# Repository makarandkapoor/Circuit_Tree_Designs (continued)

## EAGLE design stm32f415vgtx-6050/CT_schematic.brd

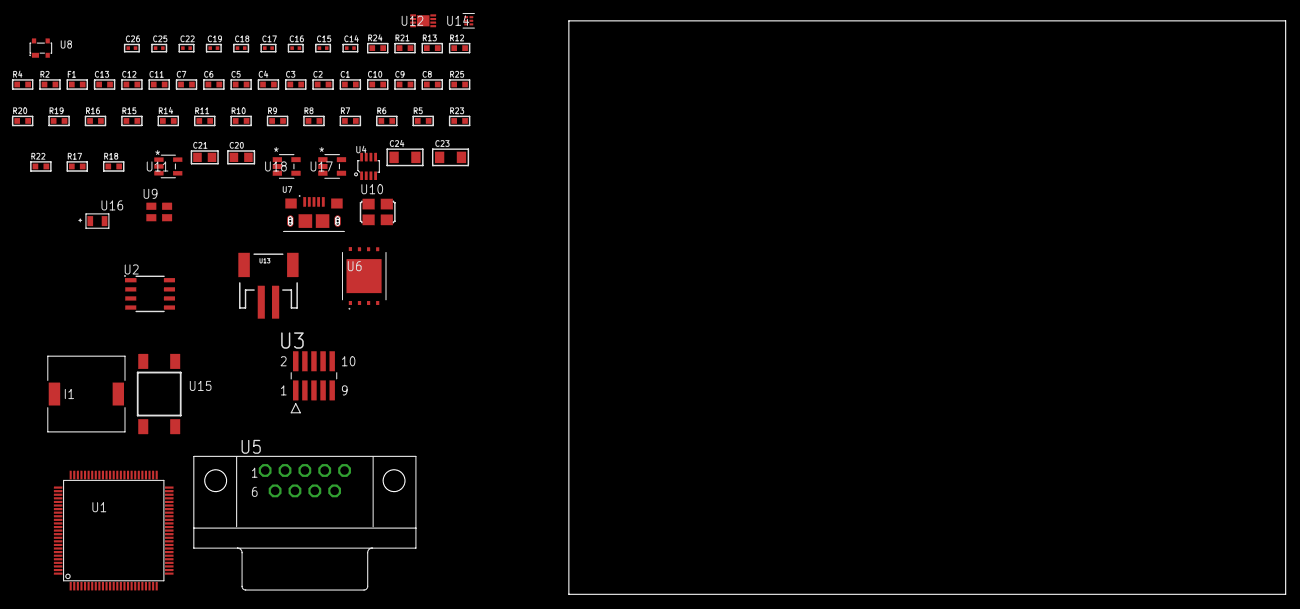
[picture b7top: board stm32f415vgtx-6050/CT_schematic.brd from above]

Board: 2 copper layers, 69 parts (0 on the bottom side), 45 nets, no tracks yet.

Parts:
C1, C12, C13: 1e-06; C0603
C2, C3, C4, C5, C6, C7: 1e-07; C0603
C8: 4.7e-06; C0603
C9, C10: 2.2e-06; C0603
C11: 1e-08; C0603
C14, C17, C18, C19, C25, C26: 1e-08; C0402
C15, C16, C22: 1e-07; C0402
C20, C21: 1e-05; C0805
C23, C24: 1e-05; C1206
F1: 240.0; L0603
I1: 2.5e-06; DR1040
R2: 1000.0; R0603
R4: 4700.0; R0603
R5, R6, R7, R8, R9, R10, R11, R14, R15, R16, R19, R20, R25: 10000.0; R0603
R12: 5.0; R0603
R13: 120.0; R0603
R17: 220000.0; R0603
R18: 1000000.0; R0603
R21: 9100.0; R0603
R22: 680000.0; R0603
R23: 120000.0; R0603
R24: 2000.0; R0603
U1: STM32F415VGT6; LQFP100
U2: AT25320B-SSHL-T; SOIC-8
U3: FTSH-105-01-L-DV-K; SAMTEC_FTSH-105-01-L-DV-K
U4: MAX3051EKA+T; SOT-23-8
U5: 182-009-113R531; 182-009-MALE
U6: S25FL128SDPNFI001; WNG008
U7: 10118193-0001LF; FCI_10118193-0001LF
U8: prtr5v0u2ax; SOT143B
U9: ASEK-32.768KHz-ECST; ASEK
U10: ASFL1-25MHZ-NCS; ASFL1
U11: ltc3406es5; TSOT-23-5
U12: MCP73831T-2ACI/MC; DFN8_2X3MC
U13: S2B-PH-SM4-TB(LF)(SN); JST-2-SMD
U14: TPS3895ADRYR; SON-6
U15: 4-1437565-2; SW_4-1437565-2
U16: Q65110A2395; LGM67K-G1J2-24-Z
U17, U18: nc7sz125m5x; NC7SZ125M5X

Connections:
CLK_U1_8: U1.8, U9.3
CLK_U1_12: U1.12, U10.3
GND: C1.2, C2.2, C3.2, C4.2, C5.2, C6.2, C7.2, C8.2, C9.2, C10.2, C11.2, C12.2, C13.2, C14.2, C15.2, C16.2, C17.2, C18.2, C19.2, C20.2, C21.1, C21.2, C22.2, C23.2, C24.2, C25.2, C26.2, R2.2, R5.2, R12.2, R17.2, R21.2, R23.2, R24.2, U1.10, U1.20, U1.27, U1.70, U1.74, U1.99, U2.4, U3.3, U3.5, U4.2, U4.8, U5.5, U6.4, U6.PAD, U7.5, U7.6, U7.7, U7.8, U7.9, U8.1, U9.2, U10.2, U11.2, U12.6, U12.9, U13.2, U14.2, U16.C, U17.2, U17.3, U18.1, U18.3
INPUT_USBPOWER_5V: C13.1, C23.1, R25.2, U1.68, U7.1, U8.4, U12.1, U12.2
NET_U1_14: R4.1, U1.14, U18.4
NET_U1_22: C11.1, C12.1, F1.1, U1.21, U1.22
NET_U1_49: C9.1, U1.49
NET_U1_73: C10.1, U1.73
NET_U1_94: R5.1, U1.94
NET_U1_98: U15.3, U15.4
NET_U2_3: R6.1, U2.3
NET_U2_7: R8.1, U2.7
NET_U3_9: R12.1, U3.9
NET_U4_6: R13.2, U4.6
NET_U5_2: R13.2, U4.6, U5.2
NET_U5_3: R13.1, U4.7, U5.3
NET_U6_3: R14.1, U6.3
NET_U6_7: R16.1, U6.7
NET_U11_3: I1.1, U11.3
NET_U11_5: R17.1, R18.1, U11.5
NET_U11_ATNET_3: I1.2, R18.2
NET_U12_5: R25.1, U12.5
NET_U12_8: R24.1, U12.8
NET_U14_1: R20.1, R21.1, U14.1
NET_U14_3: R22.2, R23.1, U14.3
NET_U14_4: R19.1, U14.4, U17.4, U18.2
NET_U15_1: R2.1, U15.1, U15.2
PROC_CAN1_RX: U1.81, U4.4
PROC_CAN1_TX: U1.82, U4.1
PROC_SPI1_MISO: U1.31, U2.2
PROC_SPI1_MOSI: U1.32, U2.5
PROC_SPI1_NSS: R7.1, U1.29, U2.1
PROC_SPI1_SCK: U1.30, U2.6
PROC_SPI2_MISO: U1.17, U6.2
PROC_SPI2_MOSI: U1.18, U6.5
PROC_SPI2_NSS: R15.1, U1.51, U6.1
PROC_SPI2_SCK: U1.47, U6.6
PROC_SYS_JTCK_SWCLK: R10.1, U1.76, U3.4
PROC_SYS_JTDO_SWO: U1.89, U3.6
PROC_SYS_JTMS_SWDIO: R11.1, U1.72, U3.2
PROC_USB_OTG_FS_DM: U1.70, U7.2, U8.3
PROC_USB_OTG_FS_DP: U1.71, U7.3, U8.2
RST_OUT_U3_JTAG_RST_B: R9.1, U3.10, U17.1
VCC_S1_3V7: C20.1, C24.1, U11.4, U12.3, U12.4, U13.1
VCC_TIER1_3V3: C1.1, C2.1, C3.1, C4.1, C5.1, C6.1, C7.1, C8.1, C14.1, C15.1, C16.1, C17.1, C18.1, C19.1, C21.2, C22.1, C25.1, C26.1, F1.2, I1.2, R4.2, R6.2, R7.2, R8.2, R9.2, R10.2, R11.2, R14.2, R15.2, R16.2, R18.2, R19.2, R20.2, R22.1, U1.6, U1.11, U1.19, U1.28, U1.50, U1.75, U1.100, U2.8, U3.1, U4.3, U6.8, U9.4, U10.4, U14.6, U17.5, U18.5

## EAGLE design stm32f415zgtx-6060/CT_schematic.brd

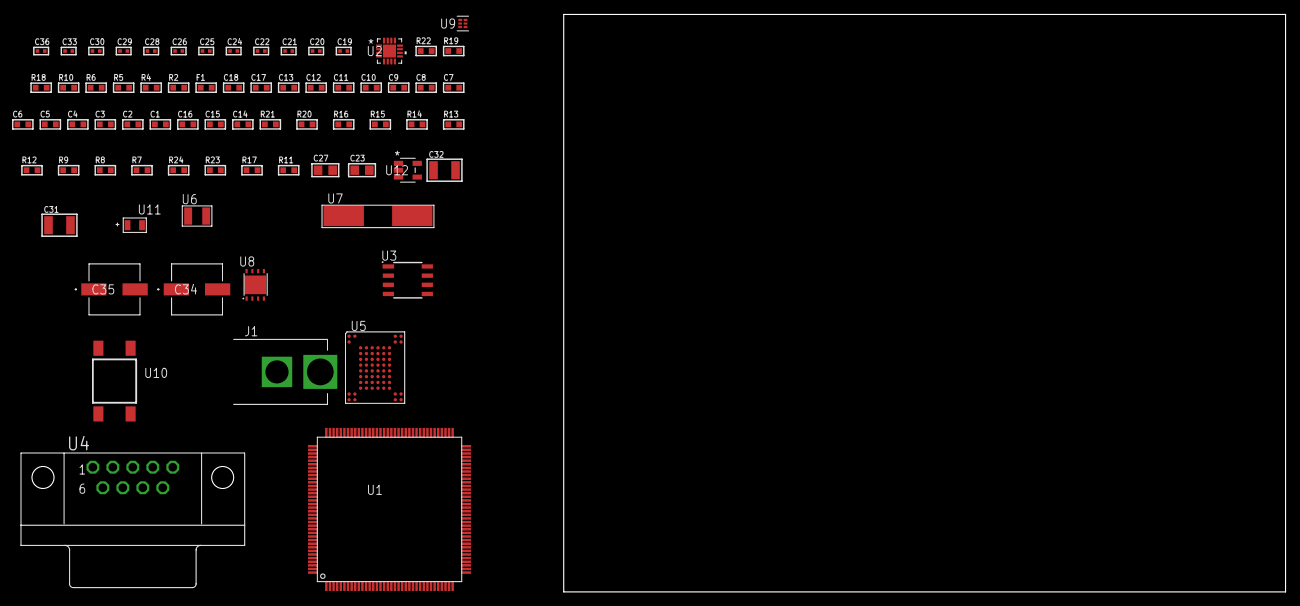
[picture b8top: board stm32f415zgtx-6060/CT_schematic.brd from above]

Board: 2 copper layers, 100.0 x 80.0 mm, 72 parts (0 on the bottom side), 46 nets, no tracks yet.

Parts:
C1, C18: 1e-06; C0603
C2, C3, C4, C5, C6, C7, C8, C9, C10, C11, C12, C13: 1e-07; C0603
C14: 4.7e-06; C0603
C15, C16: 2.2e-06; C0603
C17: 1e-08; C0603
C19, C20, C21, C22: 1e-11; C0402
C23: 4.7e-06; C0805
C24, C25, C26, C28, C29, C33: 1e-07; C0402
C27: 1e-05; C0805
C30, C36: 1e-08; C0402
C31, C32: 1e-05; C1210
C34, C35: 0.0001; EXV-9H
F1: 240.0; L0603
J1: PJ-037B; PJ-037B_PACKAGE
R2, R19: 1000.0; R0603
R4: 4700.0; R0603
R5, R6: 2200.0; R0603
R7, R8, R9, R12, R13, R14, R15, R16, R20, R21: 10000.0; R0603
R10: 120.0; R0603
R11, R17: 100000.0; R0603
R18: 2231.0; R0603
R22: 9100.0; R0603
R23: 680000.0; R0603
R24: 120000.0; R0603
U1: STM32F415ZGT6; LQFP144
U2: MMA8451QT; QFN-16
U3: SN65HVD230D; SOIC-8
U4: 182-009-113R531; 182-009-MALE
U5: TH58NVG3S0HBAI4
U6: ABS07-32.768KHZ-7-T
U7: ABLS-25.000MHZ-B2F-T
U8: LP3878SDX-ADJ/NOPB; WSON-8
U9: TPS3895ADRYR; SON-6
U10: 4-1437565-2; SW_4-1437565-2
U11: Q65110A2395; LGM67K-G1J2-24-Z
U12: nc7sz125m5x; NC7SZ125M5X

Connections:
CLK_CRYSTAL_U1_8: C19.1, U1.8, U6.1
CLK_CRYSTAL_U1_9: C20.1, U1.9, U6.2
CLK_CRYSTAL_U1_23: C21.1, U1.23, U7.1
CLK_CRYSTAL_U1_24: C22.1, U1.24, U7.2
GND: C1.2, C2.2, C3.2, C4.2, C5.2, C6.2, C7.2, C8.2, C9.2, C10.2, C11.2, C12.2, C13.2, C14.2, C15.2, C16.2, C17.2, C18.2, C19.2, C20.2, C21.2, C22.2, C23.2, C24.2, C25.2, C26.2, C27.2, C28.2, C29.2, C30.2, C31.2, C32.2, C33.2, C34.2, C35.2, C36.2, J1.2, R2.2, R8.2, R11.2, R19.2, R22.2, R24.2, U1.16, U1.31, U1.38, U1.51, U1.61, U1.83, U1.94, U1.107, U1.120, U1.130, U2.5, U2.10, U2.12, U2.17, U3.2, U4.5, U5.C5, U5.K3, U5.K8, U8.3, U8.PAD, U9.2, U11.C, U12.1, U12.3
NET_U1_25: R4.1, U1.25, U12.4
NET_U1_33: C17.1, C18.1, F1.1, U1.32, U1.33
NET_U1_71: C15.1, U1.71
NET_U1_106: C16.1, U1.106
NET_U1_136: R5.1, U1.136, U2.4
NET_U1_137: R6.1, U1.137, U2.6
NET_U1_138: R8.1, U1.138
NET_U1_142: U10.3, U10.4
NET_U1_143: R7.1, U1.143
NET_U2_2: C25.1, U2.2
NET_U2_7: R9.1, U2.7
NET_U3_6: R10.2, U3.6
NET_U3_8: R11.1, U3.8
NET_U4_2: R10.2, U3.6, U4.2
NET_U4_3: R10.1, U3.7, U4.3
NET_U5_C3: R15.1, U5.C3
NET_U8_1: C30.1, U8.1
NET_U8_6: R18.2, R19.1, U8.6
NET_U8_8: R17.1, U8.8
NET_U9_1: R21.1, R22.1, U9.1
NET_U9_3: R23.2, R24.1, U9.3
NET_U9_4: R20.1, U9.4, U12.2
NET_U10_1: R2.1, U10.1, U10.2
PROC_CAN1_RX: U1.103, U3.4
PROC_CAN1_TX: U1.104, U3.1
PROC_FSMC_A16: U1.80, U5.D5
PROC_FSMC_A17: U1.81, U5.C4
PROC_FSMC_D0: U1.85, U5.H4
PROC_FSMC_D1: U1.86, U5.J4
PROC_FSMC_D2: U1.114, U5.K4
PROC_FSMC_D3: U1.115, U5.K5
PROC_FSMC_D4: U1.58, U5.K6
PROC_FSMC_D5: U1.59, U5.J7
PROC_FSMC_D6: U1.60, U5.K7
PROC_FSMC_D7: U1.63, U5.J8
PROC_FSMC_INT2: R16.1, U1.91, U5.C8
PROC_FSMC_NCE2: R12.1, U1.123, U5.C6
PROC_FSMC_NOE: R13.1, U1.118, U5.D4
PROC_FSMC_NWE: R14.1, U1.119, U5.C7
VCC_S1_11V4: C31.1, C34.1, C35.1, J1.1, R17.2, U8.4
VCC_TIER1_3V3: C1.1, C2.1, C3.1, C4.1, C5.1, C6.1, C7.1, C8.1, C9.1, C10.1, C11.1, C12.1, C13.1, C14.1, C23.1, C24.1, C26.1, C27.1, C28.1, C29.1, C32.1, C33.1, C36.1, F1.2, R4.2, R5.2, R6.2, R7.2, R9.2, R12.2, R13.2, R14.2, R15.2, R16.2, R18.1, R20.2, R21.2, R23.1, U1.6, U1.17, U1.30, U1.39, U1.52, U1.62, U1.72, U1.84, U1.95, U1.108, U1.121, U1.131, U1.144, U2.1, U2.14, U3.3, U5.H8, U5.J6, U8.5, U9.6, U12.5
